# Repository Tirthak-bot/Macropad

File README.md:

# Macropad
A Macropad with 9 keys, A Knob and A display, all easy to customize with KMK Firmware.

# Schematic

# PCB 
The PCB was designed in KiCad and V1 was scrapped because of mismanagement of GPIO.

# Case
The case was designed in Fusion 360.

# Parts Used

1X Seeed XIAO RP2040 <br>
9X 1N4148 Diodes <br>
9X MX-Style switches <br>
1X EC11 Rotary encoder <br>
1X 0.91 inch OLED display <br>
9X DSA Keycaps <br>
4X M3x16mm screws <br>
4X M3x5mx4mm Heatset Inserts

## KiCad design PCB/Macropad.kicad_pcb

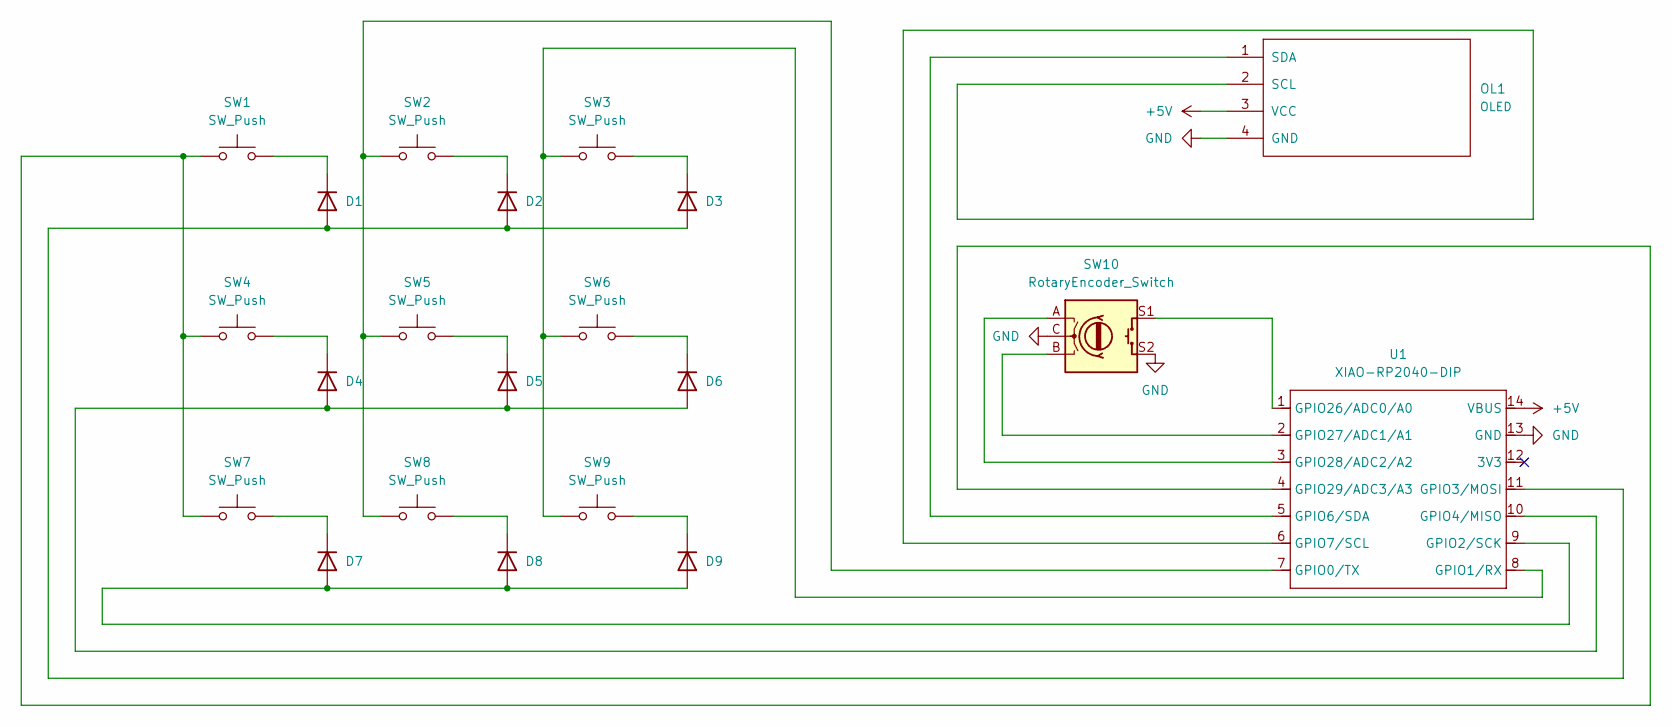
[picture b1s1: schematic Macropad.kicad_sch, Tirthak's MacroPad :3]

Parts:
D1, D2, D3, D4, D5, D6, D7, D8, D9: 1N4148; D_DO-35_SOD27_P7.62mm_Horizontal
OL1: OLED; SSD1306-0.91-OLED-4pin-128x32
SW1, SW2, SW3, SW4, SW5, SW6, SW7, SW8, SW9: SW_Push; SW_Cherry_MX_1.00u_PCB
SW10: RotaryEncoder_Switch; RotaryEncoder_Alps_EC11E-Switch_Vertical_H20mm_MountingHoles
U1: XIAO-RP2040-DIP

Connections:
+5V: OL1.3 (VCC), U1.14 (VBUS)
GND: OL1.4 (GND), SW10.C, SW10.S2, U1.13 (GND)
unnamed: D1.2 (A), D2.2 (A), D3.2 (A), U1.11 (GPIO3/MOSI)
unnamed: D1.1 (K), SW1.2
unnamed: D2.1 (K), SW2.2
unnamed: D3.1 (K), SW3.2
unnamed: D4.2 (A), D5.2 (A), D6.2 (A), U1.10 (GPIO4/MISO)
unnamed: D4.1 (K), SW4.2
unnamed: D5.1 (K), SW5.2
unnamed: D6.1 (K), SW6.2
unnamed: D7.2 (A), D8.2 (A), D9.2 (A), U1.9 (GPIO2/SCK)
unnamed: D7.1 (K), SW7.2
unnamed: D8.1 (K), SW8.2
unnamed: D9.1 (K), SW9.2
unnamed: OL1.2 (SCL), U1.6 (GPIO7/SCL)
unnamed: OL1.1 (SDA), U1.5 (GPIO6/SDA)
unnamed: SW2.1, SW5.1, SW8.1, U1.7 (GPIO0/TX)
unnamed: SW3.1, SW6.1, SW9.1, U1.8 (GPIO1/RX)
unnamed: SW10.S1, U1.1 (GPIO26/ADC0/A0)
unnamed: SW10.B, U1.2 (GPIO27/ADC1/A1)
unnamed: SW10.A, U1.3 (GPIO28/ADC2/A2)
unnamed: SW1.1, SW4.1, SW7.1, U1.4 (GPIO29/ADC3/A3)

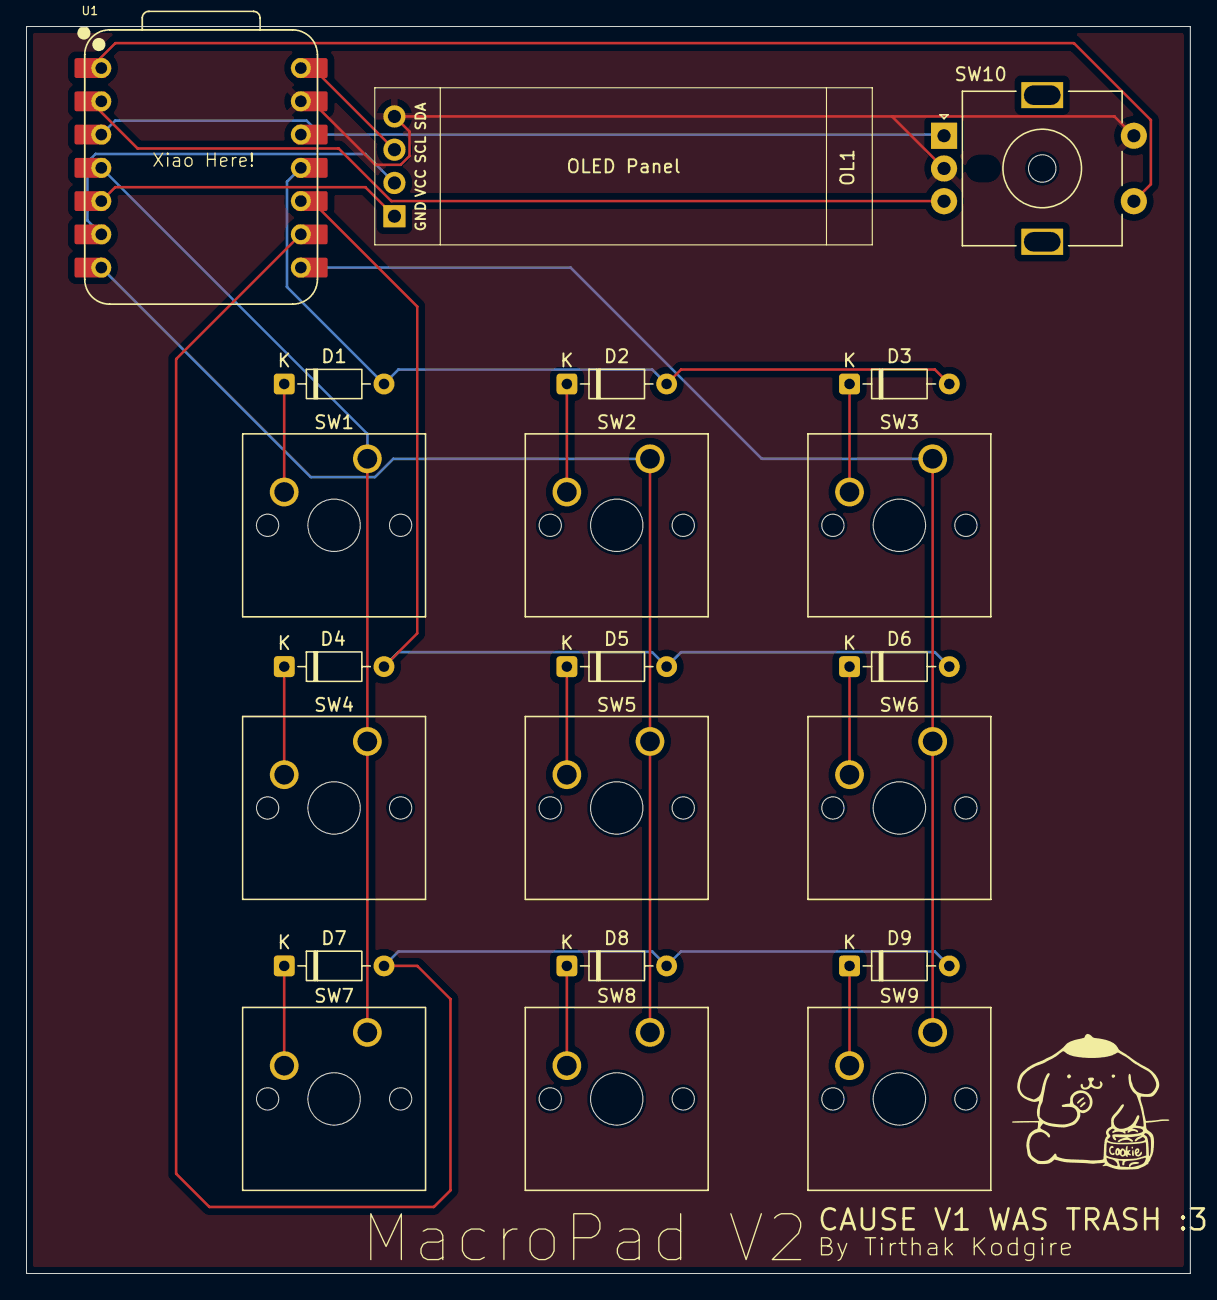
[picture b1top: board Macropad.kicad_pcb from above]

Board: 2 copper layers, 88.9 x 95.2 mm, 21 parts (0 on the bottom side), 22 nets.

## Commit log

2025-12-05 README.md
2025-12-05 TEMP
2025-12-05 Create temp
2025-12-05 Create SASN
